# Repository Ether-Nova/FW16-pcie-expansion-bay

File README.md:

# FW16-pcie-expansion-bay
My goal for this project is to be able to connect any common pcie device to the framework 16. The expansion bay would include 75W power to the gen 4 x8 (4 x16 phisical size) slot and allow pcie extenders and aother devices to be connected to it. 
I am currently in the phase of tesing a covnertor for the 12V 75W bus.

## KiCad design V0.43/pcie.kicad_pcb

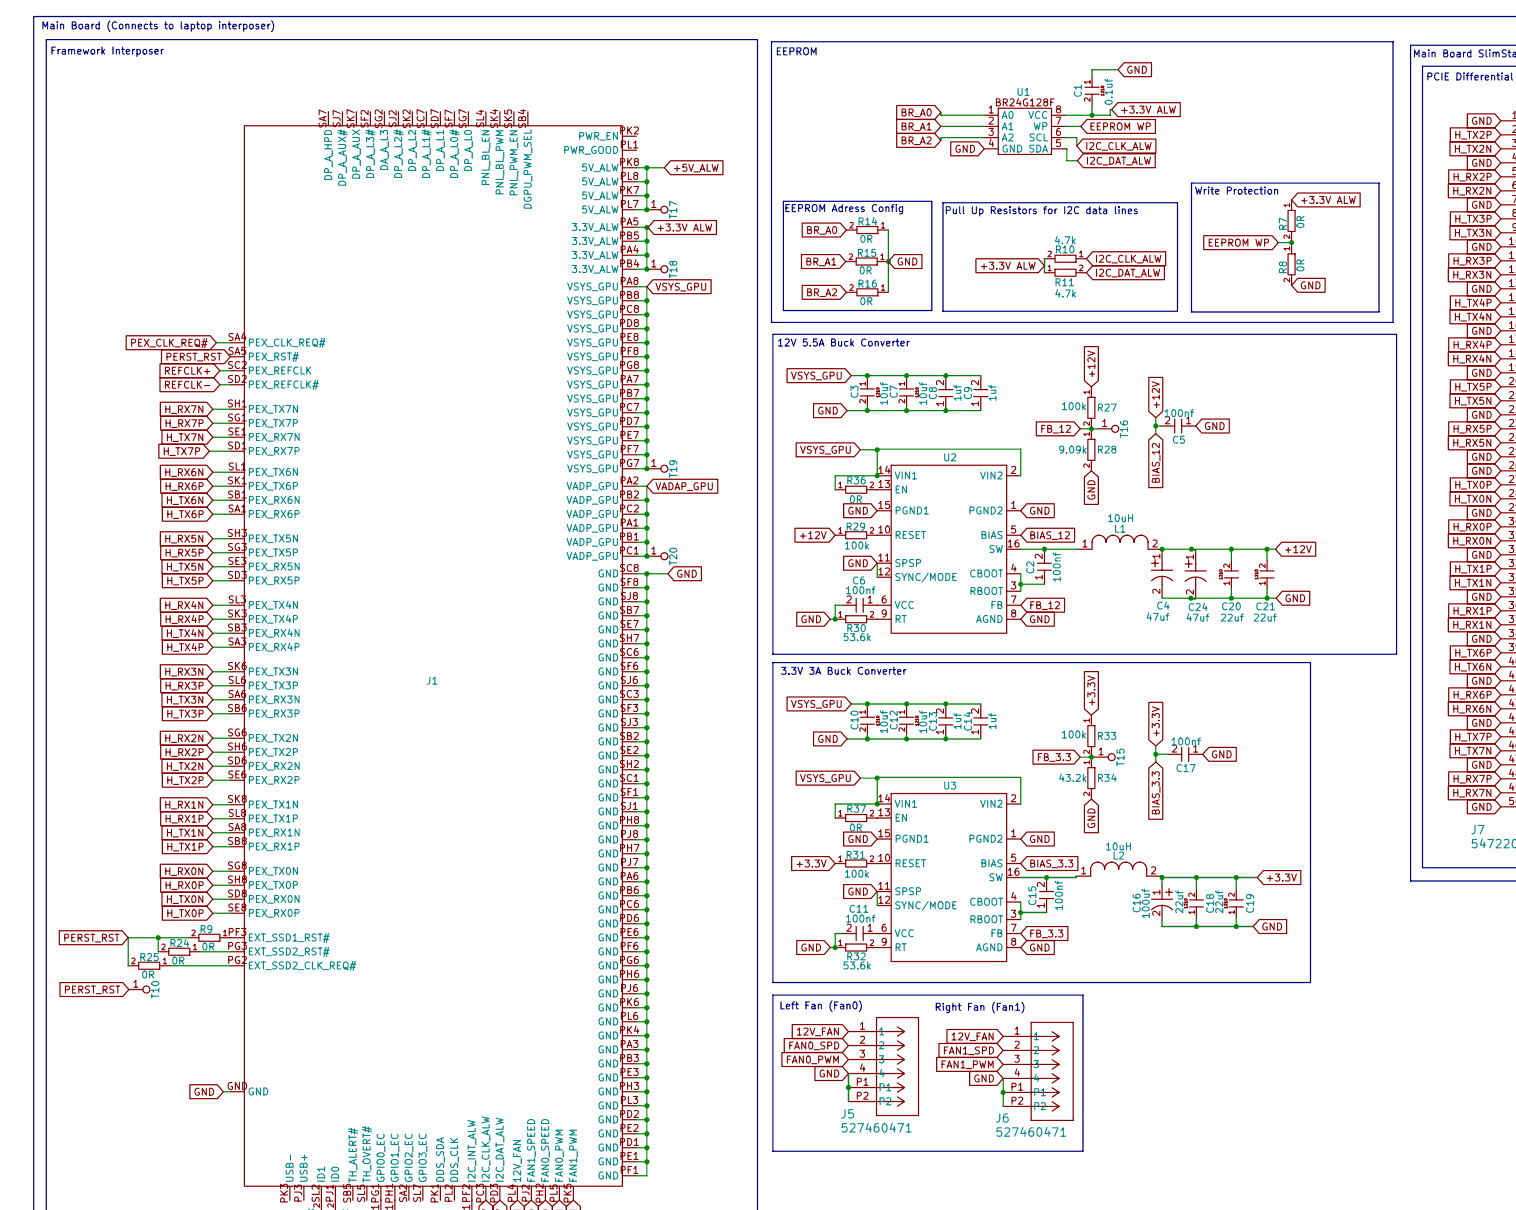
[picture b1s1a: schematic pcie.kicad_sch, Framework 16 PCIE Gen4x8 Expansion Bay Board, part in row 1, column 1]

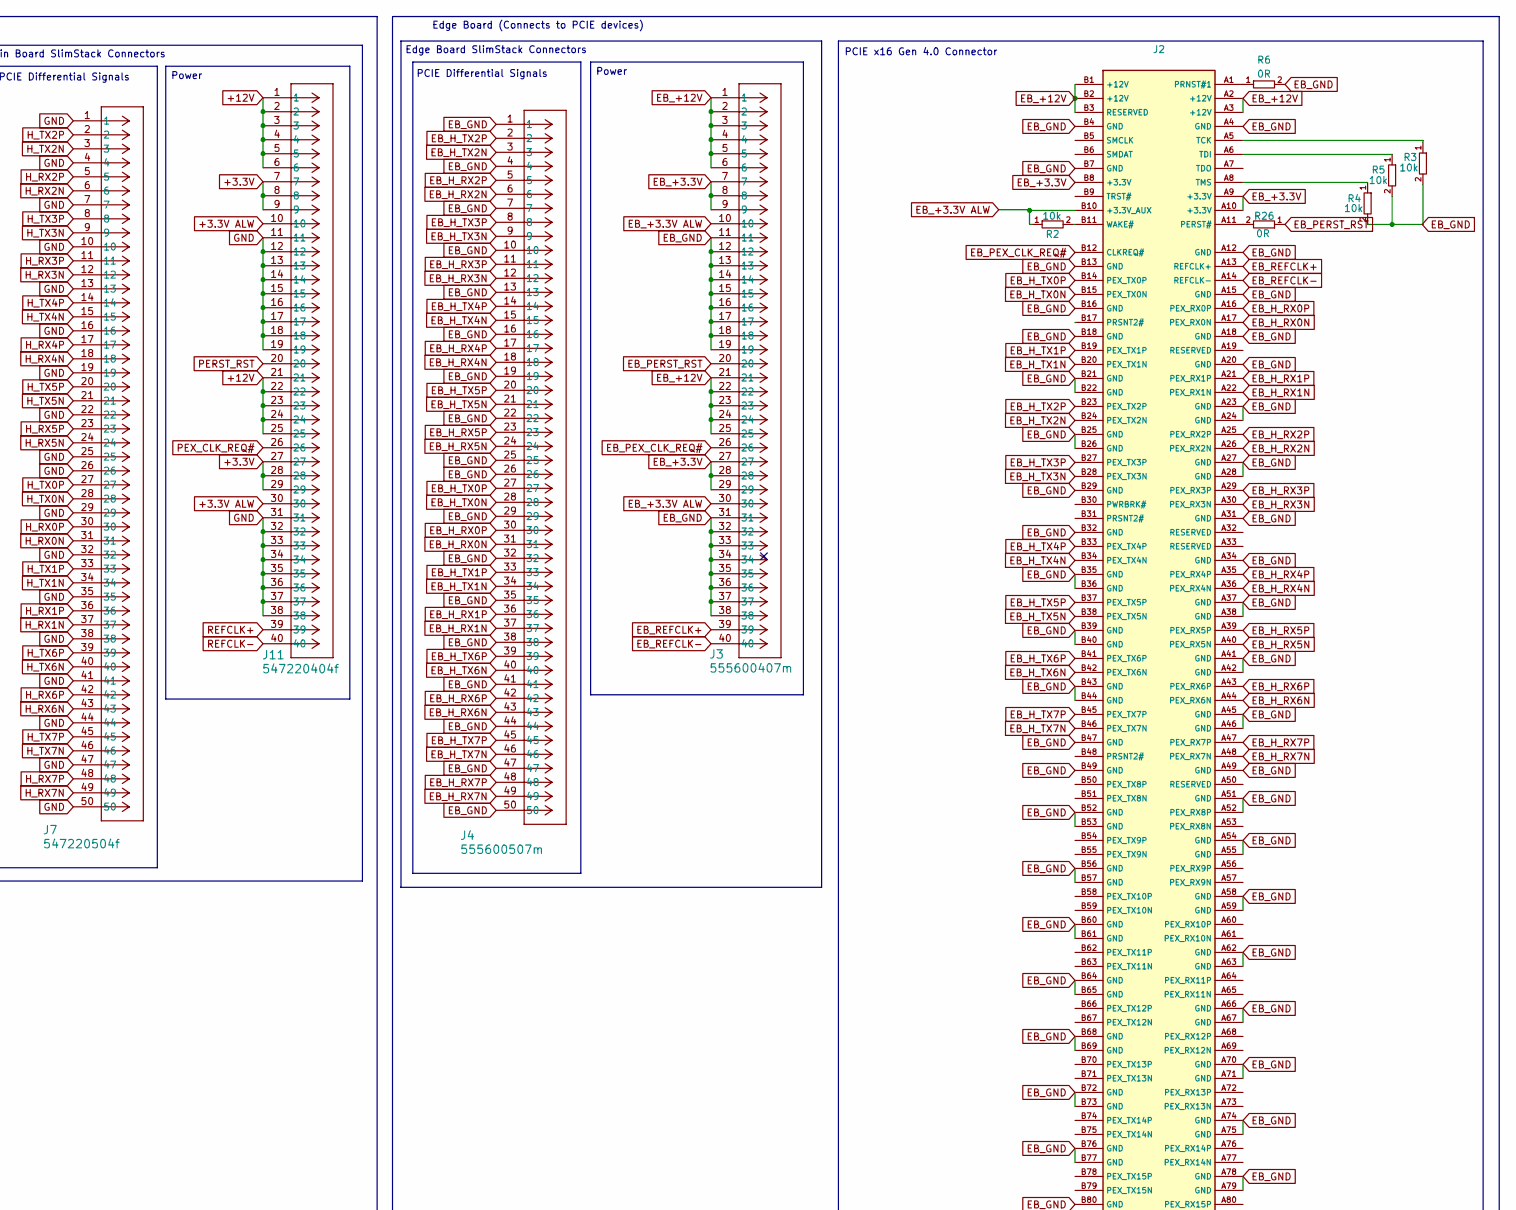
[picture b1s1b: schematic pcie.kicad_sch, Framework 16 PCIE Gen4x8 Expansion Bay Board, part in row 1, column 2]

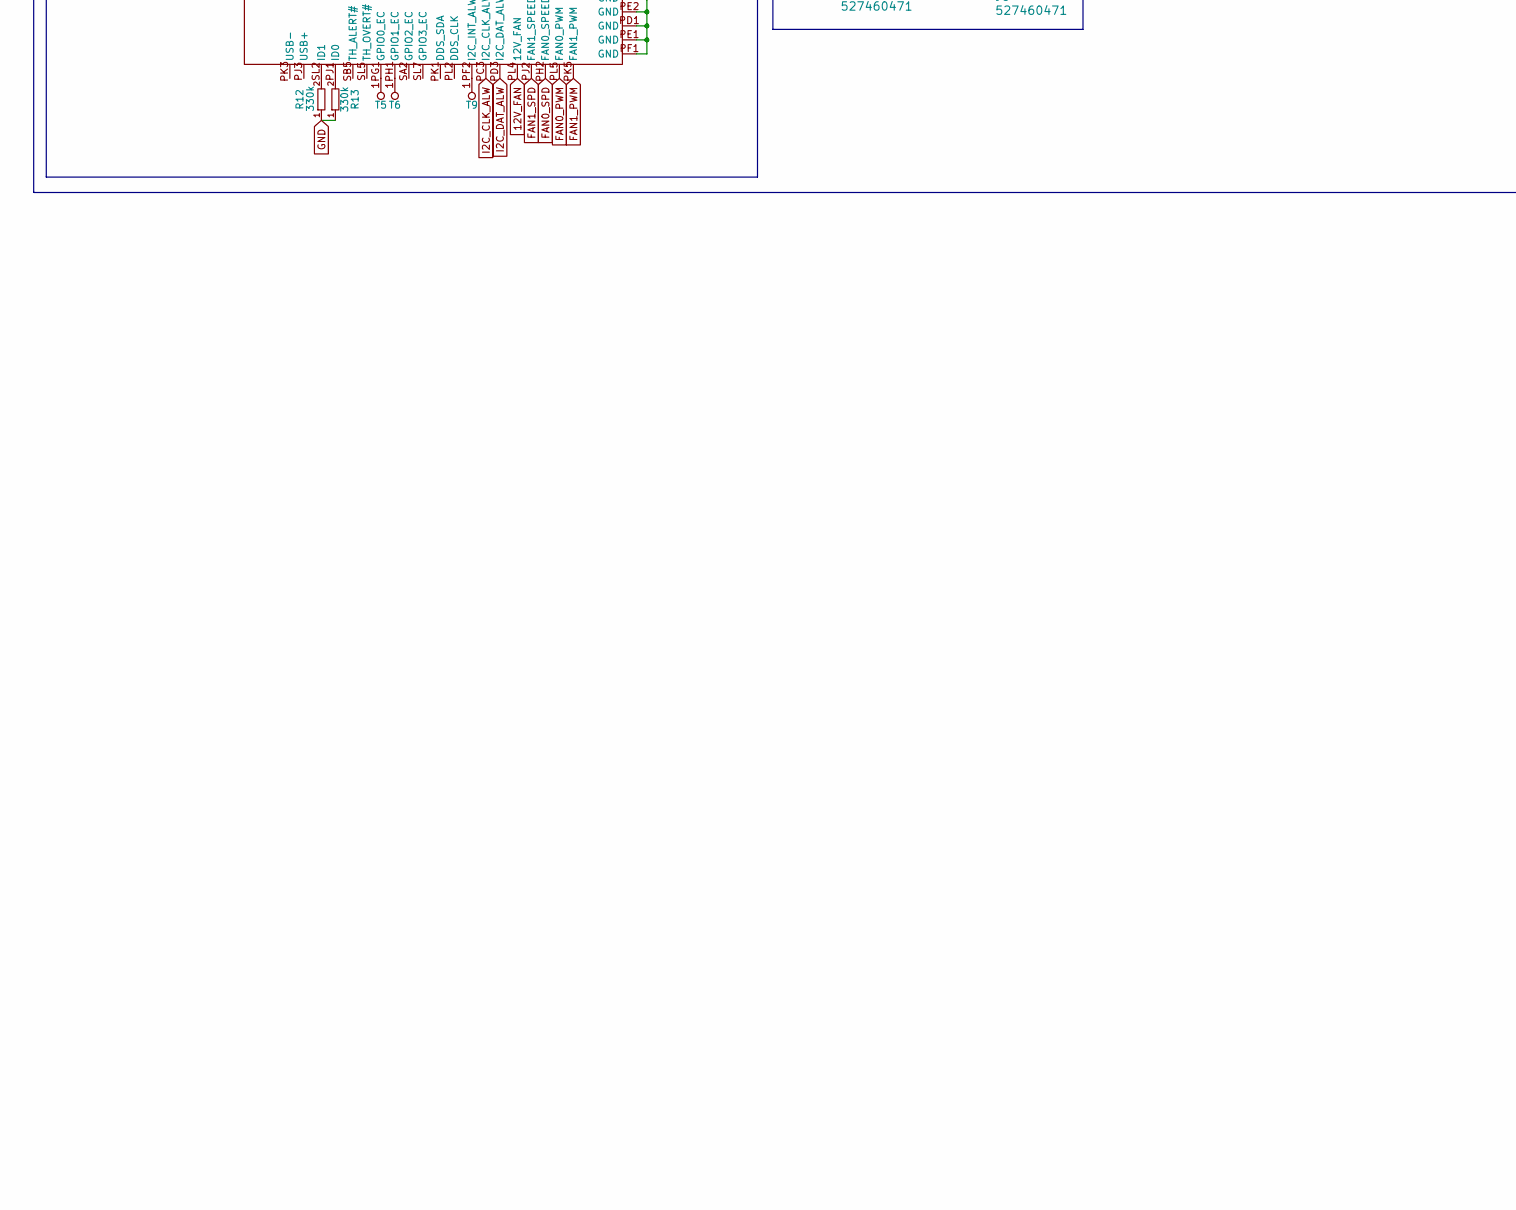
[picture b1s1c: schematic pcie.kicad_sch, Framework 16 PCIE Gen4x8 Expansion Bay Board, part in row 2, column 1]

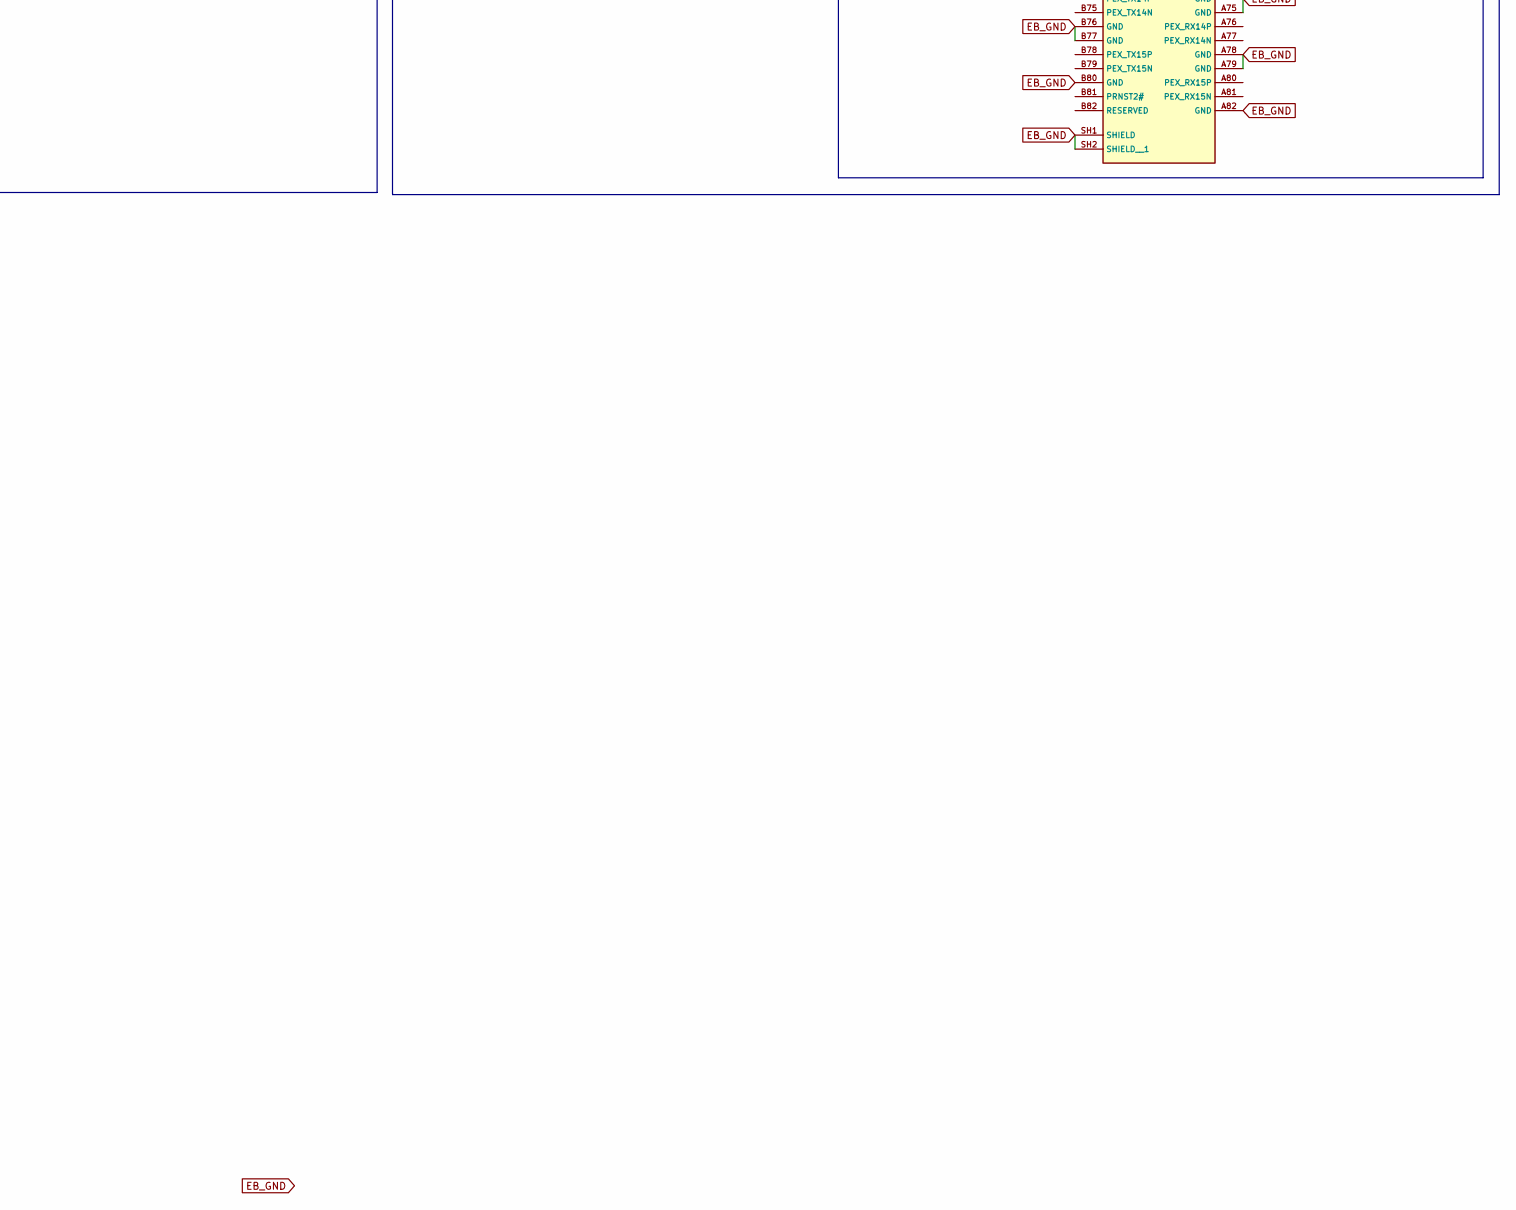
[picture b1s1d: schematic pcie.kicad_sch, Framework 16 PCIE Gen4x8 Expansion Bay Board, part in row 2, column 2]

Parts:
C1: 0.1uf; 1210 capacitor
C2, C5, C6, C11, C15, C17: 100nf; 0603
C3, C7, C10, C12: 10uf; 1210 capacitor
C4, C24: 47uf
C8, C9, C13, C14: 1uf; 0603
C16: 100uf; 100uf (cout)
C18, C19, C20, C21: 22uf; 1210 capacitor
J1: FW 16 Interposer DB
J2: PCIEx16 Edge
J3: 555600407m
J4: 555600507m; CON_555600507m
J5, J6: 527460471; 0527460471
J7: 547220504f; CON_547220504f
J11: 547220404f
L1: 10uH; 10uH (12V)
L2: 10uH; 10uH (3.3V)
R2, R3, R4, R5: 10k; 0603
R6, R7, R8, R9, R14, R15, R16, R24, R25, R26, R36, R37: 0R; 0603
R10, R11: 4.7k; 0603
R12, R13: 330k; 0603
R27, R29, R31, R33: 100k; 0603
R28: 9.09k; 0603
R30, R32: 53.6k; 0603
R34: 43.2k; 0603
T5, T6, T9, T10, T15, T16, T17, T18, T19, T20: TestPad
U1: BR24G128f
U2, U3: LM61480

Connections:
12V_FAN: J1.PL4 (12V_FAN), J5.1, J6.1
+3.3V: C16.1, C17.2, C18.2, C19.2, J11.7, J11.8, J11.9, J11.27, J11.28, J11.29, L2.2, R31.1, R33.1, U3.5 (BIAS)
+3.3V ALW: C1.2, J1.PA4 (3.3V_ALW), J1.PA5 (3.3V_ALW), J1.PB4 (3.3V_ALW), J1.PB5 (3.3V_ALW), J11.10, J11.30, R7.1, R10.2, R11.1, T18.1, U1.8 (VCC)
+5V_ALW: J1.PK7 (5V_ALW), J1.PK8 (5V_ALW), J1.PL7 (5V_ALW), J1.PL8 (5V_ALW), T17.1
+12V: C4.1, C5.2, C20.2, C21.2, C24.1, J11.1, J11.2, J11.3, J11.4, J11.5, J11.6, J11.21, J11.22, J11.23, J11.24, J11.25, L1.2, R27.1, R29.1, U2.5 (BIAS)
BR_A0: R14.2, U1.1 (A0)
BR_A1: R15.2, U1.2 (A1)
BR_A2: R16.2, U1.3 (A2)
EB_+3.3V: J2.A9 (+3.3V), J2.A10 (+3.3V), J2.B8 (+3.3V), J3.7, J3.8, J3.9, J3.27, J3.28, J3.29
EB_+3.3V ALW: J2.B10 (+3.3V_AUX), J3.10, J3.30, R2.1
EB_+12V: J2.A2 (+12V), J2.A3 (+12V), J2.B1 (+12V), J2.B2 (+12V), J2.B3 (RESERVED), J3.1, J3.2, J3.3, J3.4, J3.5, J3.6, J3.21, J3.22, J3.23, J3.24, J3.25
EB_GND: J2.A4 (GND), J2.A12 (GND), J2.A15 (GND), J2.A18 (GND), J2.A20 (GND), J2.A23 (GND), J2.A24 (GND), J2.A27 (GND), J2.A28 (GND), J2.A31 (GND), J2.A34 (GND), J2.A37 (GND), J2.A38 (GND), J2.A41 (GND), J2.A42 (GND), J2.A45 (GND), J2.A46 (GND), J2.A49 (GND), J2.A51 (GND), J2.A52 (PEX_RX8P), J2.A54 (GND), J2.A55 (GND), J2.A58 (GND), J2.A59 (GND), J2.A62 (GND), J2.A63 (GND), J2.A66 (GND), J2.A67 (GND), J2.A70 (GND), J2.A71 (GND), J2.A74 (GND), J2.A75 (GND), J2.A78 (GND), J2.A79 (GND), J2.A82 (GND), J2.B4 (GND), J2.B7 (GND), J2.B13 (GND), J2.B16 (GND), J2.B18 (GND), J2.B21 (GND), J2.B22 (GND), J2.B25 (GND), J2.B26 (GND), J2.B29 (GND), J2.B32 (GND), J2.B35 (GND), J2.B36 (GND), J2.B39 (GND), J2.B40 (GND), J2.B43 (GND), J2.B44 (GND), J2.B47 (GND), J2.B49 (GND), J2.B52 (GND), J2.B53 (GND), J2.B56 (GND), J2.B57 (GND), J2.B60 (GND), J2.B61 (GND), J2.B64 (GND), J2.B65 (GND), J2.B68 (GND), J2.B69 (GND), J2.B72 (GND), J2.B73 (GND), J2.B76 (GND), J2.B77 (GND), J2.B80 (GND), J2.SH1 (SHIELD), J2.SH2 (SHIELD__1), J3.11, J3.12, J3.13, J3.14, J3.15, J3.16, J3.17, J3.18, J3.19, J3.31, J3.32, J3.33, J3.34, J3.35, J3.36, J3.37, J3.38, J4.1, J4.4, J4.7, J4.10, J4.13, J4.16, J4.19, J4.22, J4.25, J4.26, J4.29, J4.32, J4.35, J4.38, J4.41, J4.44, J4.47, J4.50, R3.2, R4.2, R5.2, R6.2
EB_H_RX0N: J2.A17 (PEX_RX0N), J4.31
EB_H_RX0P: J2.A16 (PEX_RX0P), J4.30
EB_H_RX1N: J2.A22 (PEX_RX1N), J4.37
EB_H_RX1P: J2.A21 (PEX_RX1P), J4.36
EB_H_RX2N: J2.A26 (PEX_RX2N), J4.6
EB_H_RX2P: J2.A25 (PEX_RX2P), J4.5
EB_H_RX3N: J2.A30 (PEX_RX3N), J4.12
EB_H_RX3P: J2.A29 (PEX_RX3P), J4.11
EB_H_RX4N: J2.A36 (PEX_RX4N), J4.18
EB_H_RX4P: J2.A35 (PEX_RX4P), J4.17
EB_H_RX5N: J2.A40 (PEX_RX5N), J4.24
EB_H_RX5P: J2.A39 (PEX_RX5P), J4.23
EB_H_RX6N: J2.A44 (PEX_RX6N), J4.43
EB_H_RX6P: J2.A43 (PEX_RX6P), J4.42
EB_H_RX7N: J2.A48 (PEX_RX7N), J4.49
EB_H_RX7P: J2.A47 (PEX_RX7P), J4.48
EB_H_TX0N: J2.B15 (PEX_TX0N), J4.28
EB_H_TX0P: J2.B14 (PEX_TX0P), J4.27
EB_H_TX1N: J2.B20 (PEX_TX1N), J4.34
EB_H_TX1P: J2.B19 (PEX_TX1P), J4.33
EB_H_TX2N: J2.B24 (PEX_TX2N), J4.3
EB_H_TX2P: J2.B23 (PEX_TX2P), J4.2
EB_H_TX3N: J2.B28 (PEX_TX3N), J4.9
EB_H_TX3P: J2.B27 (PEX_TX3P), J4.8
EB_H_TX4N: J2.B34 (PEX_TX4N), J4.15
EB_H_TX4P: J2.B33 (PEX_TX4P), J4.14
EB_H_TX5N: J2.B38 (PEX_TX5N), J4.21
EB_H_TX5P: J2.B37 (PEX_TX5P), J4.20
EB_H_TX6N: J2.B42 (PEX_TX6N), J4.40
EB_H_TX6P: J2.B41 (PEX_TX6P), J4.39
EB_H_TX7N: J2.B46 (PEX_TX7N), J4.46
EB_H_TX7P: J2.B45 (PEX_TX7P), J4.45
EB_PERST_RST: J3.20, R26.1
EB_PEX_CLK_REQ#: J2.B12 (CLKREQ#), J3.26
EB_REFCLK+: J2.A13 (REFCLK+), J3.39
EB_REFCLK-: J2.A14 (REFCLK-), J3.40
EEPROM WP: R7.2, R8.1, U1.7 (WP)
FAN0_PWM: J1.PL5 (FAN0_PWM), J5.3
FAN0_SPD: J1.PH2 (FAN0_SPEED), J5.2
FAN1_PWM: J1.PK5 (FAN1_PWM), J6.3
FAN1_SPD: J1.PJ2 (FAN1_SPEED), J6.2
FB_3.3: R33.2, R34.1, T15.1, U3.7 (FB)
FB_12: R27.2, R28.1, T16.1, U2.7 (FB)
GND: C1.1, C3.2, C4.2, C5.1, C6.2, C7.2, C8.1, C9.1, C10.2, C11.2, C12.2, C13.1, C14.1, C16.2, C17.1, C18.1, C19.1, C20.1, C21.1, C24.2, J1.GND, J1.PA3 (GND), J1.PA6 (GND), J1.PB3 (GND), J1.PB6 (GND), J1.PC6 (GND), J1.PD1 (GND), J1.PD2 (GND), J1.PD6 (GND), J1.PE1 (GND), J1.PE2 (GND), J1.PE3 (GND), J1.PE6 (GND), J1.PF1 (GND), J1.PF6 (GND), J1.PG6 (GND), J1.PH3 (GND), J1.PH6 (GND), J1.PH7 (GND), J1.PH8 (GND), J1.PJ6 (GND), J1.PJ7 (GND), J1.PJ8 (GND), J1.PK4 (GND), J1.PK6 (GND), J1.PL3 (GND), J1.PL6 (GND), J1.SB2 (GND), J1.SB7 (GND), J1.SC1 (GND), J1.SC3 (GND), J1.SC6 (GND), J1.SC8 (GND), J1.SE2 (GND), J1.SE7 (GND), J1.SF1 (GND), J1.SF3 (GND), J1.SF6 (GND), J1.SF8 (GND), J1.SH2 (GND), J1.SH7 (GND), J1.SJ1 (GND), J1.SJ3 (GND), J1.SJ6 (GND), J1.SJ8 (GND), J5.4, J5.P1, J5.P2, J6.4, J6.P1, J6.P2, J7.1, J7.4, J7.7, J7.10, J7.13, J7.16, J7.19, J7.22, J7.25, J7.26, J7.29, J7.32, J7.35, J7.38, J7.41, J7.44, J7.47, J7.50, J11.11, J11.12, J11.13, J11.14, J11.15, J11.16, J11.17, J11.18, J11.19, J11.31, J11.32, J11.33, J11.34, J11.35, J11.36, J11.37, J11.38, R8.2, R12.1, R13.1, R14.1, R15.1, R16.1, R28.2, R30.1, R32.1, R34.2, U1.4 (GND), U2.1 (PGND2), U2.8 (AGND), U2.11 (SPSP), U2.12 (SYNC/MODE), U2.15 (PGND1), U3.1 (PGND2), U3.8 (AGND), U3.11 (SPSP), U3.12 (SYNC/MODE), U3.15 (PGND1)
H_RX0N: J1.SG8 (PEX_TX0N), J7.31
H_RX0P: J1.SH8 (PEX_TX0P), J7.30
H_RX1N: J1.SK8 (PEX_TX1N), J7.37
H_RX1P: J1.SL8 (PEX_TX1P), J7.36
H_RX2N: J1.SG6 (PEX_TX2N), J7.6
H_RX2P: J1.SH6 (PEX_TX2P), J7.5
H_RX3N: J1.SK6 (PEX_TX3N), J7.12
H_RX3P: J1.SL6 (PEX_TX3P), J7.11
H_RX4N: J1.SL3 (PEX_TX4N), J7.18
H_RX4P: J1.SK3 (PEX_TX4P), J7.17
H_RX5N: J1.SH3 (PEX_TX5N), J7.24
H_RX5P: J1.SG3 (PEX_TX5P), J7.23
H_RX6N: J1.SL1 (PEX_TX6N), J7.43
H_RX6P: J1.SK1 (PEX_TX6P), J7.42
H_RX7N: J1.SH1 (PEX_TX7N), J7.49
H_RX7P: J1.SG1 (PEX_TX7P), J7.48
H_TX0N: J1.SD8 (PEX_RX0N), J7.28
H_TX0P: J1.SE8 (PEX_RX0P), J7.27
H_TX1N: J1.SA8 (PEX_RX1N), J7.34
H_TX1P: J1.SB8 (PEX_RX1P), J7.33
H_TX2N: J1.SD6 (PEX_RX2N), J7.3
H_TX2P: J1.SE6 (PEX_RX2P), J7.2
H_TX3N: J1.SA6 (PEX_RX3N), J7.9
H_TX3P: J1.SB6 (PEX_RX3P), J7.8
H_TX4N: J1.SB3 (PEX_RX4N), J7.15
H_TX4P: J1.SA3 (PEX_RX4P), J7.14
H_TX5N: J1.SE3 (PEX_RX5N), J7.21
H_TX5P: J1.SD3 (PEX_RX5P), J7.20
H_TX6N: J1.SB1 (PEX_RX6N), J7.40
H_TX6P: J1.SA1 (PEX_RX6P), J7.39
H_TX7N: J1.SE1 (PEX_RX7N), J7.46
H_TX7P: J1.SD1 (PEX_RX7P), J7.45
I2C_CLK_ALW: J1.PC3 (I2C_CLK_ALW), R10.1, U1.6 (SCL)
I2C_DAT_ALW: J1.PD3 (I2C_DAT_ALW), R11.2, U1.5 (SDA)
unnamed: J1.PF3 (EXT_SSD1_RST#), R9.1
unnamed: J1.PG2 (EXT_SSD2_CLK_REQ#), R25.1
unnamed: J1.PG3 (EXT_SSD2_RST#), R24.1
unnamed: J1.PG1 (GPIO0_EC), T5.1
unnamed: J1.PH1 (GPIO1_EC), T6.1
unnamed: J1.PF2 (I2C_INT_ALW), T9.1
unnamed: J1.PJ1 (ID0), R13.2
unnamed: J1.SL2 (ID1), R12.2
unnamed: J2.A11 (PERST#), R26.2
unnamed: J2.A1 (PRNST#1), R6.1
unnamed: J2.A5 (TCK), R3.1
unnamed: J2.A6 (TDI), R5.1
unnamed: J2.A8 (TMS), R4.1
unnamed: J2.B11 (WAKE#), R2.2
unnamed: C2.1, U2.3 (RBOOT), U2.4 (CBOOT)
unnamed: R36.2, U2.13 (EN)
unnamed: R29.2, U2.10 (RESET)
unnamed: R30.2, U2.9 (RT)
unnamed: C2.2, L1.1, U2.16 (SW)
unnamed: C6.1, U2.6 (VCC)
unnamed: C15.1, U3.3 (RBOOT), U3.4 (CBOOT)
unnamed: R37.2, U3.13 (EN)
unnamed: R31.2, U3.10 (RESET)
unnamed: R32.2, U3.9 (RT)
unnamed: C15.2, L2.1, U3.16 (SW)
unnamed: C11.1, U3.6 (VCC)
PERST_RST: J1.SA5 (PEX_RST#), J11.20, R9.2, R24.2, R25.2, T10.1
PEX_CLK_REQ#: J1.SA4 (PEX_CLK_REQ#), J11.26
REFCLK+: J1.SC2 (PEX_REFCLK), J11.39
REFCLK-: J1.SD2 (PEX_REFCLK#), J11.40
VADAP_GPU: J1.PA1 (VADP_GPU), J1.PA2 (VADP_GPU), J1.PB1 (VADP_GPU), J1.PB2 (VADP_GPU), J1.PC1 (VADP_GPU), J1.PC2 (VADP_GPU), T20.1
VSYS_GPU: C3.1, C7.1, C8.2, C9.2, C10.1, C12.1, C13.2, C14.2, J1.PA7 (VSYS_GPU), J1.PA8 (VSYS_GPU), J1.PB7 (VSYS_GPU), J1.PB8 (VSYS_GPU), J1.PC7 (VSYS_GPU), J1.PC8 (VSYS_GPU), J1.PD7 (VSYS_GPU), J1.PD8 (VSYS_GPU), J1.PE7 (VSYS_GPU), J1.PE8 (VSYS_GPU), J1.PF7 (VSYS_GPU), J1.PF8 (VSYS_GPU), J1.PG7 (VSYS_GPU), J1.PG8 (VSYS_GPU), R36.1, R37.1, T19.1, U2.2 (VIN2), U2.14 (VIN1), U3.2 (VIN2), U3.14 (VIN1)

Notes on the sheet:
Pull Up Resistors for I2C data lines
PCIE x16 Gen 4.0 Connector
Write Protection
PCIE Differential Signals
EEPROM Adress Config
Main Board (Connects to laptop interposer)
3.3V 3A Buck Converter
Right Fan (Fan1)
Edge Board SlimStack Connectors
Main Board SlimStack Connectors
Edge Board (Connects to PCIE devices)
12V 5.5A Buck Converter
Framework Interposer
EEPROM
Left Fan (Fan0)
Power

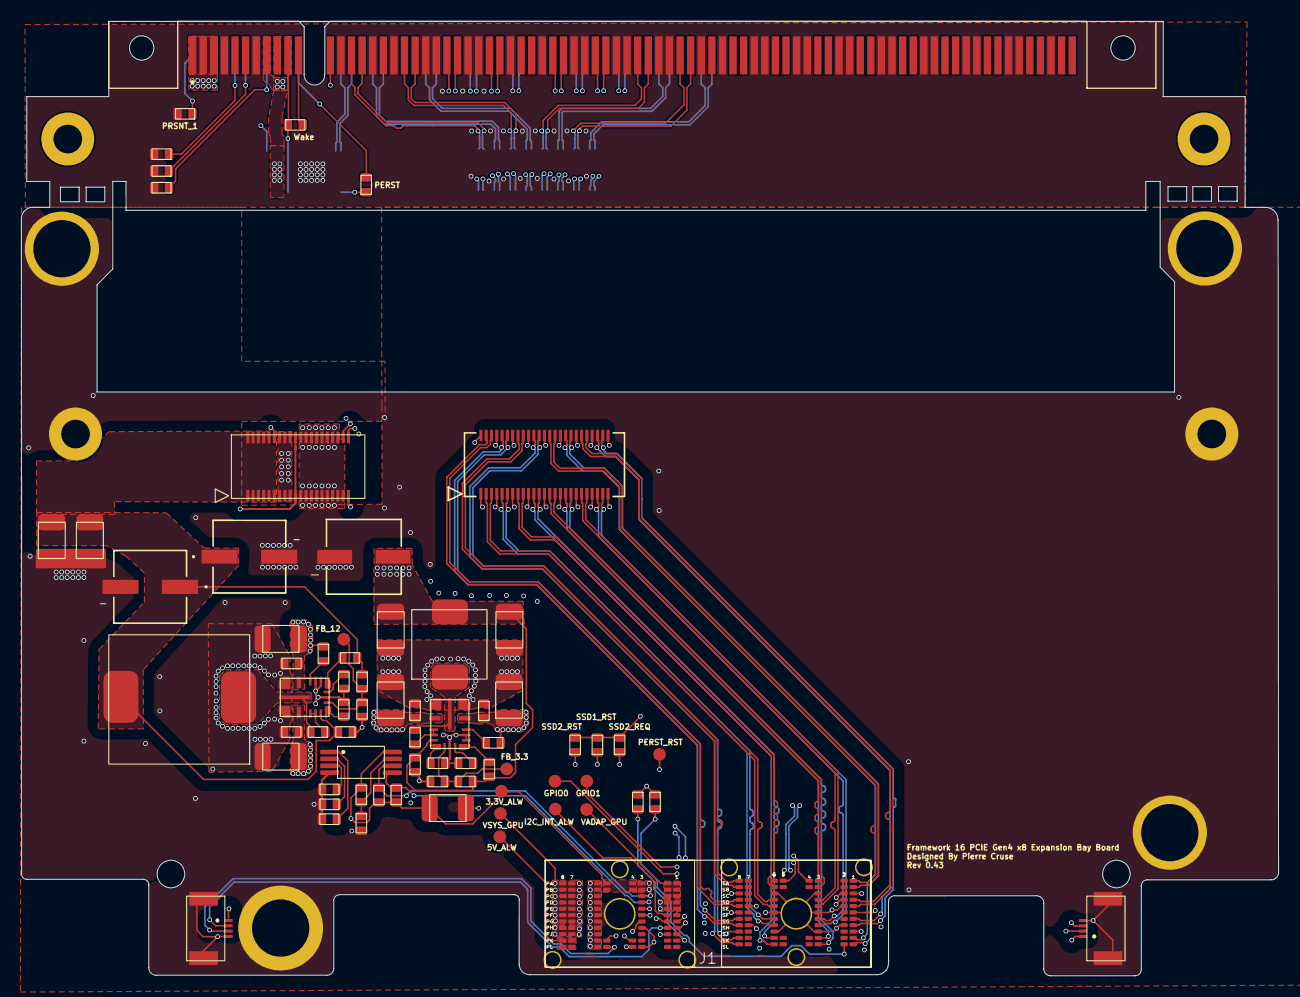
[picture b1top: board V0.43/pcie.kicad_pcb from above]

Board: 4 copper layers, 118.6 x 90.0 mm, 73 parts (0 on the bottom side), 122 nets.

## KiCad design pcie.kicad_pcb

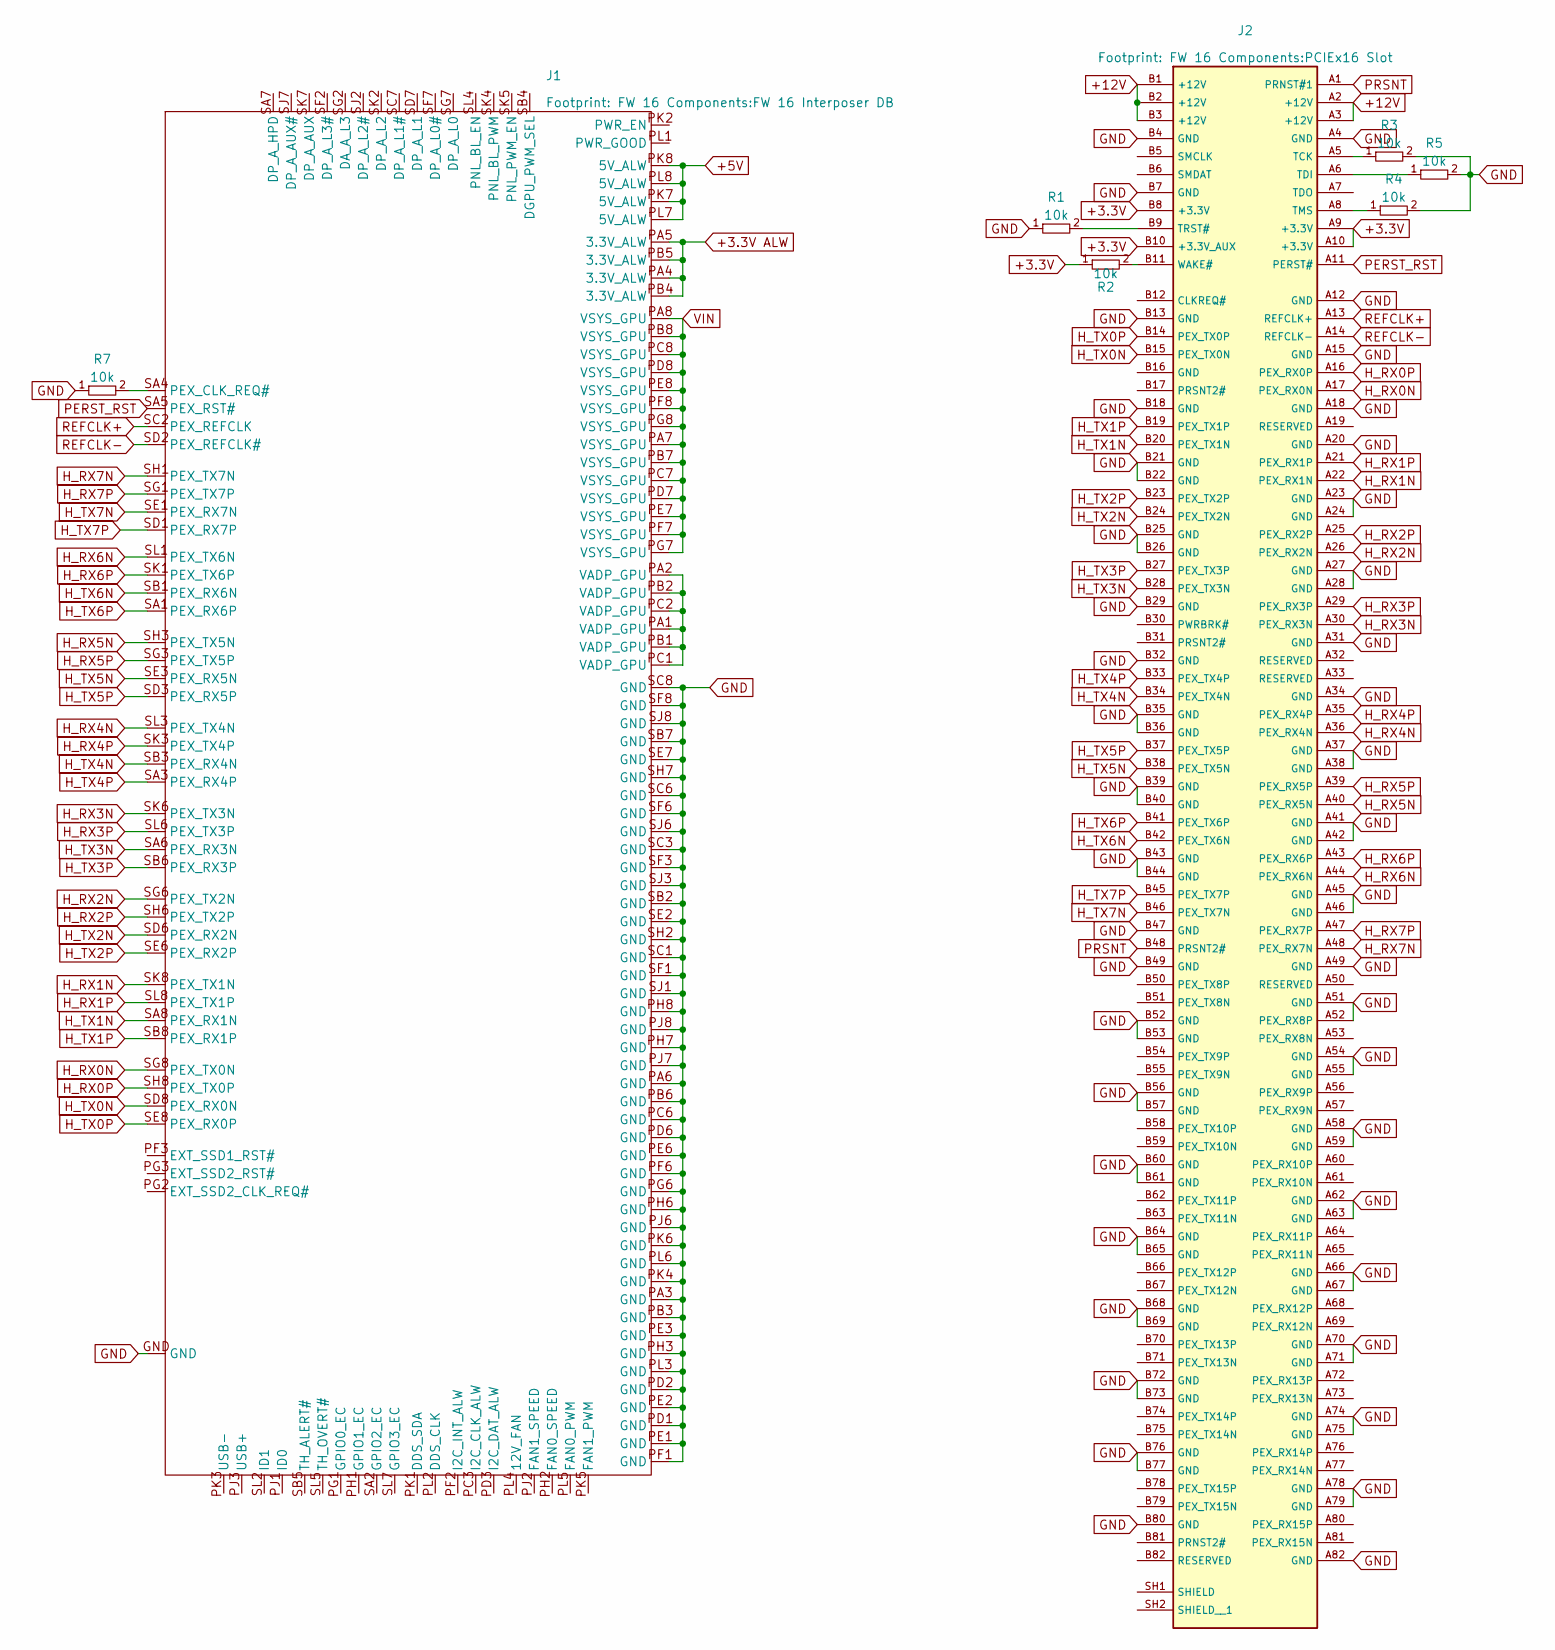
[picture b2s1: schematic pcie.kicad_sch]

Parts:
J1: FW 16 Interposer DB
J2: PCIEx16 Slot
R1, R2, R3, R4, R5, R7: 10k; 0603

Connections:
+3.3V: J2.A9 (+3.3V), J2.A10 (+3.3V), J2.B8 (+3.3V), J2.B10 (+3.3V_AUX), R2.1
+3.3V ALW: J1.PA4 (3.3V_ALW), J1.PA5 (3.3V_ALW), J1.PB4 (3.3V_ALW), J1.PB5 (3.3V_ALW)
+5V: J1.PK7 (5V_ALW), J1.PK8 (5V_ALW), J1.PL7 (5V_ALW), J1.PL8 (5V_ALW)
+12V: J2.A2 (+12V), J2.A3 (+12V), J2.B1 (+12V), J2.B2 (+12V), J2.B3 (+12V)
GND: J1.GND, J1.PA3 (GND), J1.PA6 (GND), J1.PB3 (GND), J1.PB6 (GND), J1.PC6 (GND), J1.PD1 (GND), J1.PD2 (GND), J1.PD6 (GND), J1.PE1 (GND), J1.PE2 (GND), J1.PE3 (GND), J1.PE6 (GND), J1.PF1 (GND), J1.PF6 (GND), J1.PG6 (GND), J1.PH3 (GND), J1.PH6 (GND), J1.PH7 (GND), J1.PH8 (GND), J1.PJ6 (GND), J1.PJ7 (GND), J1.PJ8 (GND), J1.PK4 (GND), J1.PK6 (GND), J1.PL3 (GND), J1.PL6 (GND), J1.SB2 (GND), J1.SB7 (GND), J1.SC1 (GND), J1.SC3 (GND), J1.SC6 (GND), J1.SC8 (GND), J1.SE2 (GND), J1.SE7 (GND), J1.SF1 (GND), J1.SF3 (GND), J1.SF6 (GND), J1.SF8 (GND), J1.SH2 (GND), J1.SH7 (GND), J1.SJ1 (GND), J1.SJ3 (GND), J1.SJ6 (GND), J1.SJ8 (GND), J2.A4 (GND), J2.A12 (GND), J2.A15 (GND), J2.A18 (GND), J2.A20 (GND), J2.A23 (GND), J2.A24 (GND), J2.A27 (GND), J2.A28 (GND), J2.A31 (GND), J2.A34 (GND), J2.A37 (GND), J2.A38 (GND), J2.A41 (GND), J2.A42 (GND), J2.A45 (GND), J2.A46 (GND), J2.A49 (GND), J2.A51 (GND), J2.A52 (PEX_RX8P), J2.A54 (GND), J2.A55 (GND), J2.A58 (GND), J2.A59 (GND), J2.A62 (GND), J2.A63 (GND), J2.A66 (GND), J2.A67 (GND), J2.A70 (GND), J2.A71 (GND), J2.A74 (GND), J2.A75 (GND), J2.A78 (GND), J2.A79 (GND), J2.A82 (GND), J2.B4 (GND), J2.B7 (GND), J2.B13 (GND), J2.B18 (GND), J2.B21 (GND), J2.B22 (GND), J2.B25 (GND), J2.B26 (GND), J2.B29 (GND), J2.B32 (GND), J2.B35 (GND), J2.B36 (GND), J2.B39 (GND), J2.B40 (GND), J2.B43 (GND), J2.B44 (GND), J2.B47 (GND), J2.B49 (GND), J2.B52 (GND), J2.B53 (GND), J2.B56 (GND), J2.B57 (GND), J2.B60 (GND), J2.B61 (GND), J2.B64 (GND), J2.B65 (GND), J2.B68 (GND), J2.B69 (GND), J2.B72 (GND), J2.B73 (GND), J2.B76 (GND), J2.B77 (GND), J2.B80 (GND), J2.S1, J2.S2, R1.1, R3.2, R4.2, R5.2, R7.1
H_RX0N: J1.SG8 (PEX_TX0N), J2.A17 (PEX_RX0N)
H_RX0P: J1.SH8 (PEX_TX0P), J2.A16 (PEX_RX0P)
H_RX1N: J1.SK8 (PEX_TX1N), J2.A22 (PEX_RX1N)
H_RX1P: J1.SL8 (PEX_TX1P), J2.A21 (PEX_RX1P)
H_RX2N: J1.SG6 (PEX_TX2N), J2.A26 (PEX_RX2N)
H_RX2P: J1.SH6 (PEX_TX2P), J2.A25 (PEX_RX2P)
H_RX3N: J1.SK6 (PEX_TX3N), J2.A30 (PEX_RX3N)
H_RX3P: J1.SL6 (PEX_TX3P), J2.A29 (PEX_RX3P)
H_RX4N: J1.SL3 (PEX_TX4N), J2.A36 (PEX_RX4N)
H_RX4P: J1.SK3 (PEX_TX4P), J2.A35 (PEX_RX4P)
H_RX5N: J1.SH3 (PEX_TX5N), J2.A40 (PEX_RX5N)
H_RX5P: J1.SG3 (PEX_TX5P), J2.A39 (PEX_RX5P)
H_RX6N: J1.SL1 (PEX_TX6N), J2.A44 (PEX_RX6N)
H_RX6P: J1.SK1 (PEX_TX6P), J2.A43 (PEX_RX6P)
H_RX7N: J1.SH1 (PEX_TX7N), J2.A48 (PEX_RX7N)
H_RX7P: J1.SG1 (PEX_TX7P), J2.A47 (PEX_RX7P)
H_TX0N: J1.SD8 (PEX_RX0N), J2.B15 (PEX_TX0N)
H_TX0P: J1.SE8 (PEX_RX0P), J2.B14 (PEX_TX0P)
H_TX1N: J1.SA8 (PEX_RX1N), J2.B20 (PEX_TX1N)
H_TX1P: J1.SB8 (PEX_RX1P), J2.B19 (PEX_TX1P)
H_TX2N: J1.SD6 (PEX_RX2N), J2.B24 (PEX_TX2N)
H_TX2P: J1.SE6 (PEX_RX2P), J2.B23 (PEX_TX2P)
H_TX3N: J1.SA6 (PEX_RX3N), J2.B28 (PEX_TX3N)
H_TX3P: J1.SB6 (PEX_RX3P), J2.B27 (PEX_TX3P)
H_TX4N: J1.SB3 (PEX_RX4N), J2.B34 (PEX_TX4N)
H_TX4P: J1.SA3 (PEX_RX4P), J2.B33 (PEX_TX4P)
H_TX5N: J1.SE3 (PEX_RX5N), J2.B38 (PEX_TX5N)
H_TX5P: J1.SD3 (PEX_RX5P), J2.B37 (PEX_TX5P)
H_TX6N: J1.SB1 (PEX_RX6N), J2.B42 (PEX_TX6N)
H_TX6P: J1.SA1 (PEX_RX6P), J2.B41 (PEX_TX6P)
H_TX7N: J1.SE1 (PEX_RX7N), J2.B46 (PEX_TX7N)
H_TX7P: J1.SD1 (PEX_RX7P), J2.B45 (PEX_TX7P)
unnamed: J1.SA4 (PEX_CLK_REQ#), R7.2
unnamed: J1.PA1 (VADP_GPU), J1.PA2 (VADP_GPU), J1.PB1 (VADP_GPU), J1.PB2 (VADP_GPU), J1.PC1 (VADP_GPU), J1.PC2 (VADP_GPU)
unnamed: J2.A5 (TCK), R3.1
unnamed: J2.A6 (TDI), R5.1
unnamed: J2.A8 (TMS), R4.1
unnamed: J2.B9 (TRST#), R1.2
unnamed: J2.B11 (WAKE#), R2.2
PERST_RST: J1.SA5 (PEX_RST#), J2.A11 (PERST#)
PRSNT: J2.A1 (PRNST#1), J2.B48 (PRSNT2#)
REFCLK+: J1.SC2 (PEX_REFCLK), J2.A13 (REFCLK+)
REFCLK-: J1.SD2 (PEX_REFCLK#), J2.A14 (REFCLK-)
VIN: J1.PA7 (VSYS_GPU), J1.PA8 (VSYS_GPU), J1.PB7 (VSYS_GPU), J1.PB8 (VSYS_GPU), J1.PC7 (VSYS_GPU), J1.PC8 (VSYS_GPU), J1.PD7 (VSYS_GPU), J1.PD8 (VSYS_GPU), J1.PE7 (VSYS_GPU), J1.PE8 (VSYS_GPU), J1.PF7 (VSYS_GPU), J1.PF8 (VSYS_GPU), J1.PG7 (VSYS_GPU), J1.PG8 (VSYS_GPU)

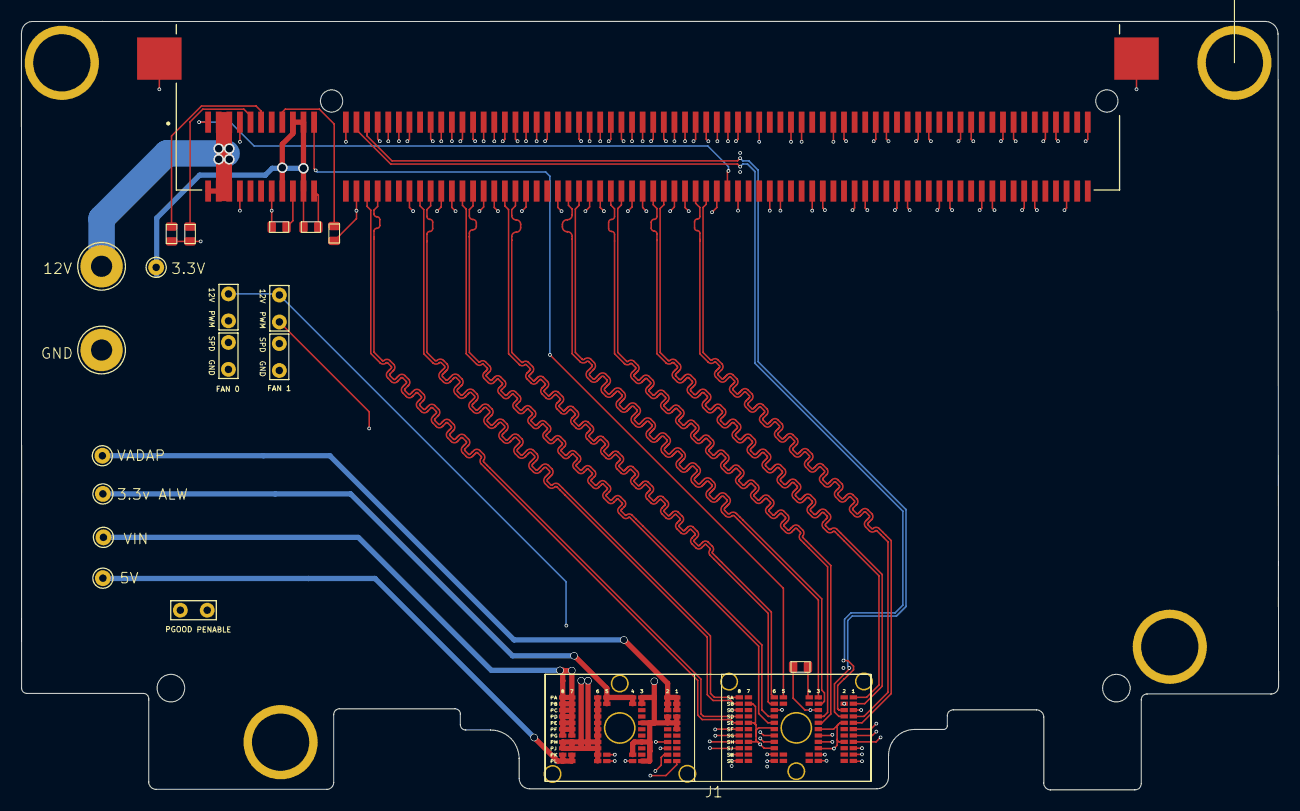
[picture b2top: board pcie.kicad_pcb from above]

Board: 4 copper layers, 118.6 x 72.5 mm, 8 parts (0 on the bottom side), 49 nets.

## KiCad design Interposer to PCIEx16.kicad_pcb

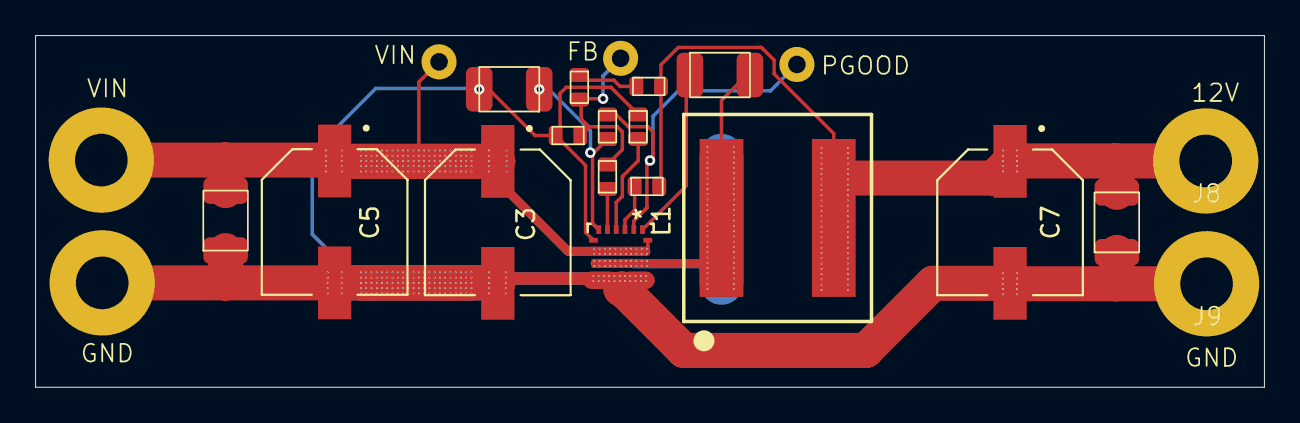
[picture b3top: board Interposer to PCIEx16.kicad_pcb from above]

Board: 2 copper layers, 70.0 x 20.0 mm, 23 parts (0 on the bottom side), 12 nets.

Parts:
C1: 1.0uf; 1210 capacitor
C2, C4, C6: .1uf; 1210 capacitor
C3, C5, C7: 100uf; 25SVPF100M
J3, J4, J5: TestPad
J6, J7, J8, J9: PowerTHT
L1: WE-XHMA_1090
R6: 47.5k; 0603
R7: 100k; 0603
R8, R9, R12: 10k; 0603
R10, R13: 10; 0603
U3: BD9F800MUX-ZE2; VQFN11_ROM

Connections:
+12V: C6.2, C7.1, J8.1, L1.2, R6.1, R10.2
GND: C1.2, C3.2, C4.1, C5.2, C6.1, C7.2, J7.1, J9.1, R8.2, R12.2, U3.7 (GND), U3.10 (PGND)
unnamed: J4.1, R7.2, R8.1, R13.2
unnamed: R6.2, R7.1
unnamed: C2.1, U3.1 (BOOT)
unnamed: R13.1, U3.5 (FB)
unnamed: R12.1, U3.4 (FREQ)
unnamed: J3.1, R9.1, U3.2 (PGD)
unnamed: R10.1, U3.3 (VOUT)
SW: C2.2, L1.1, U3.9 (SW)
VIN: C3.1, C4.2, C5.1, J5.1, J6.1, U3.8 (VIN), U3.11 (EN)
VREG: C1.1, R9.2, U3.6 (VREG)

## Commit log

2025-04-11 README.md
2025-06-17 Add files via upload
    V0.2
2025-08-15 Create README and OLD folder
2025-08-15 New PCB design
2026-01-15 V0.4 Added
2026-01-22 v0.42
    Fixed interposer footprint and cleaned up schematic
2026-03-24 V0.43
    Changed board-board connectors to ones that are easier to solder by hand
